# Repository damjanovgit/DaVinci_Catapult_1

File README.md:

# DaVinci_Catapult_1

This project is done as practical part of subjects Computer electronics and Microcontroller systems in academic 2022/23 year, winter semester. 
For realisation, we had to design PCB with all components that we need to control stepper motors, which are used to position the catapult, then limit switches and lasers, and the final result, our catapult, is shown on picture below.
<p align="center">

## Connection instructions

### PCB power supply

First, we need to connect 12V supply to PCB, and we use proto-board as voltage source to input pins of LM317. Black wire is connected to the ground, and red one to +12V. (Note: on this proto-board is written that it gives +15V but in reality it is +12V voltage source, so it is recommended to always check all sources with multimeter).
<p align="center">

 ### Connecting Picket3 programmer to PCB
 
 For programming microcontroller we use Picket3 programmer, and it has 5 wires that need to be connected in proper way. At the pictures bellow we have shown Picket3 pinout and its connection to PCB.
 <p align="center">

 ### Stepper motor and laser connection
 Six stepper motors were used to operate the catapult. Of that number, two stepper motors are used to move the lasers, the remaining four are on the catapult itself.
 Connectors for stepper motors are marked with numbers 1, 2, 3 and 4 and they need to be placed as it is shown on the picture.
 Two connectors that are next to these are used for lasers, and it is important that whichever laser we connect next to connector 4 is considered as upper laser(goes on the left side of catapult).
 <p align="center">

 Power supply for lasers is connected as it is shown on next picture, wires for every laser go in pairs (+ -, + -). Next to this we connect limit switches(next 4 pins).
 
  <p align="center">

 ### Connecting to a computer
 
 For this, we use USB to UART converter that allows us to connect a device with a UART interface to a computer via a USB port.
  <p align="center">

When everything is propperly connected, it is necessary to enable the programming of the microcontroller on the board, and after this has been successfully completed, we can control the catapult. Controlling the catapult and lasers is done by entering appropriate characters into the serial communication terminal. The table below represents the commands with the corresponding characters and description.

| Command | Functionality |
| :------: | :------: | 
| a | Laser 1 left rotation |
| d | Laser 1 right rotation |
| s | Stop laser 1 rotation |
| j | Laser 2 left rotation |
| l | Laser 2 right rotation |
| k | Stop laser 2 rotation |
| c | Calibration |
| f | Launch |
| p | Positioning of the catapult |
| b | Rotate catapult left |
| m | Rotate catapult right |
| n | Stop rotating |
| z | Tension management |
| u | Tension management |
| i | Firing |
| o | Firing |

Using the commands a, d, j and l we control the lasers by turning them left or right until we aim at the target. When the laser rays are intersected, it means that the target is aimed, and we stop their movement with the s and k commands. Once we have determined the position of the target, we use the p command to position the catapult so that it is ready for launch. Then, use command f to fire a cannonball. Using the b, m, n, z, u, i, o commands, manual control of all other motors is enabled for testing purposes.

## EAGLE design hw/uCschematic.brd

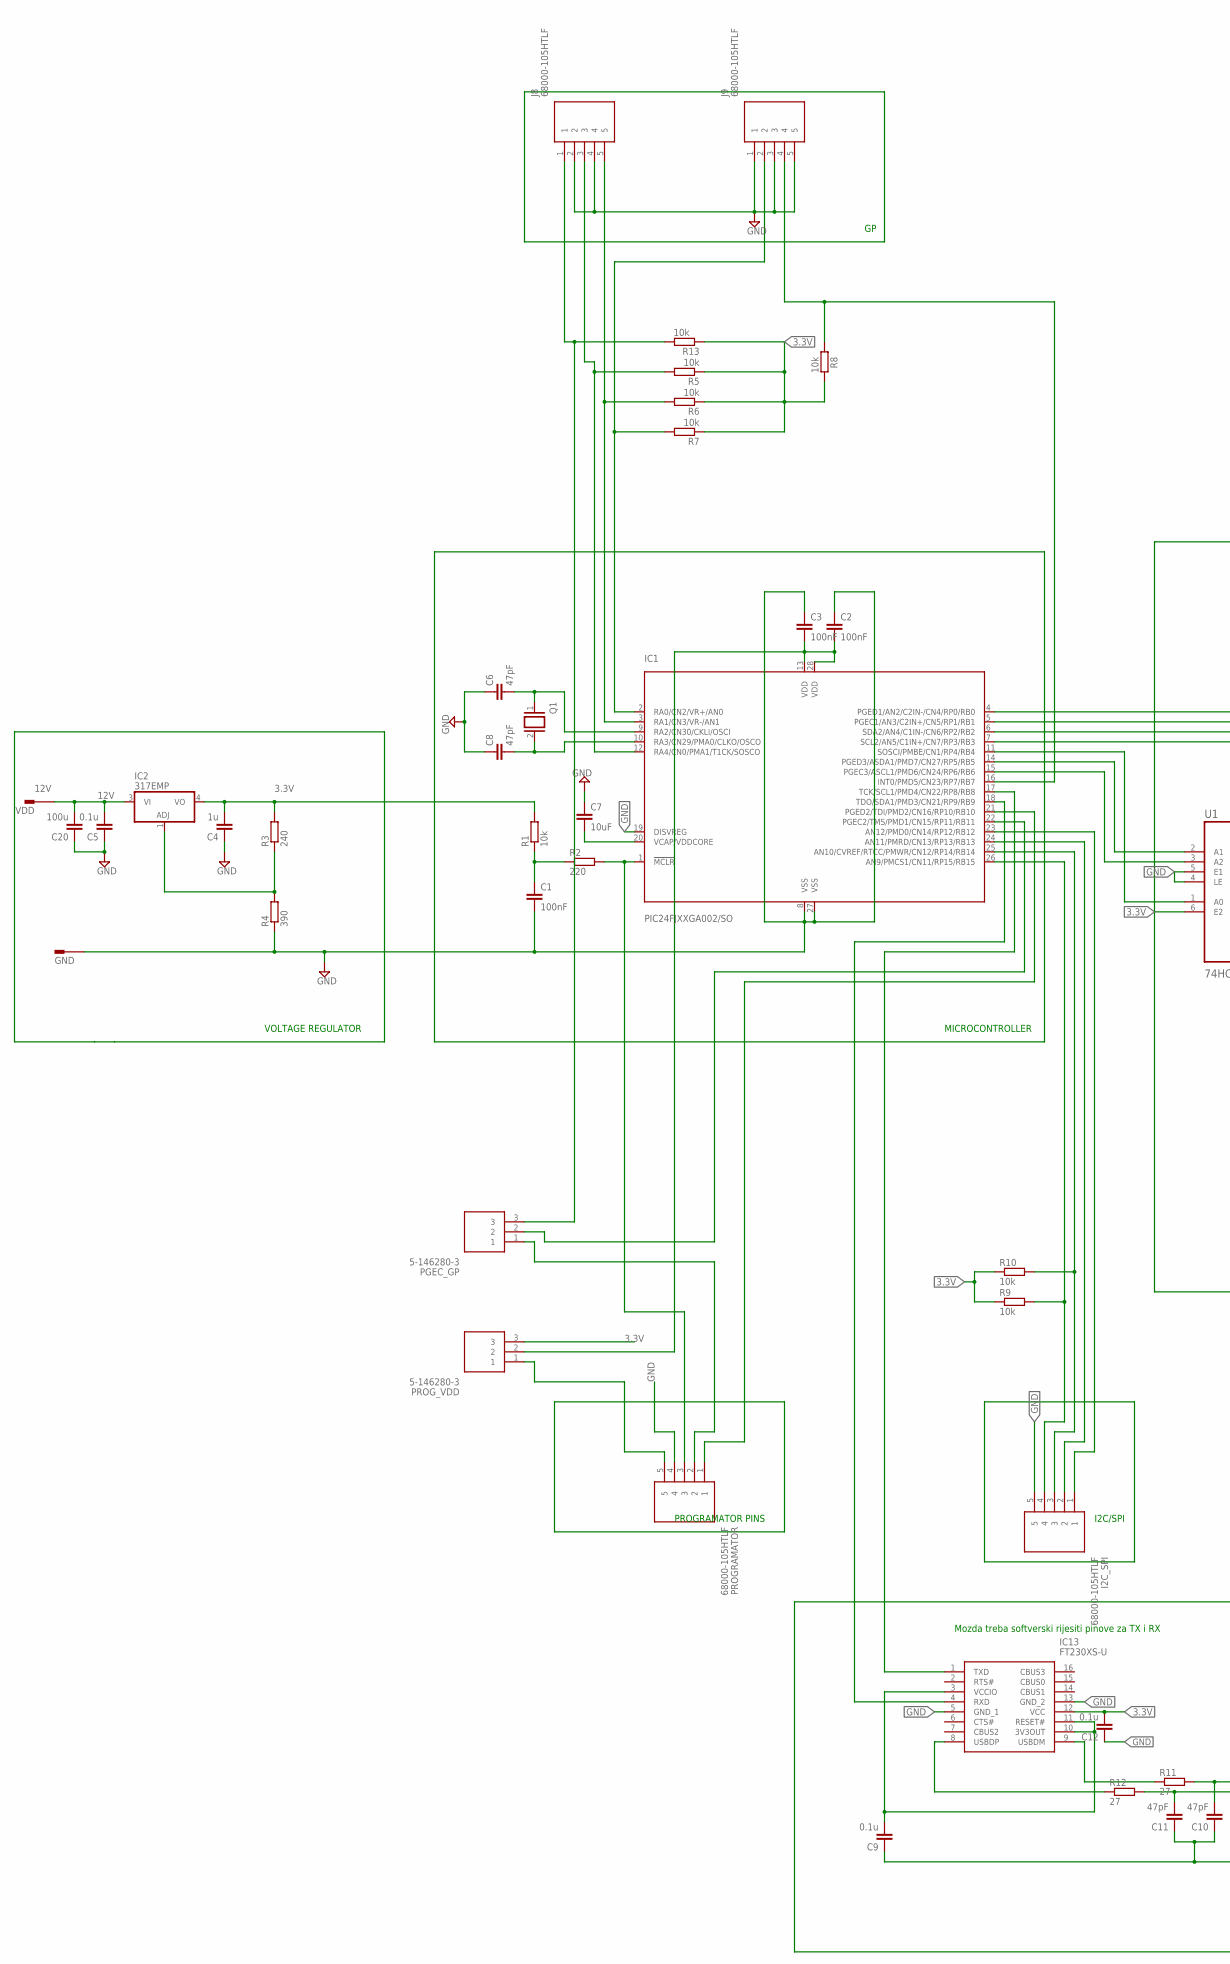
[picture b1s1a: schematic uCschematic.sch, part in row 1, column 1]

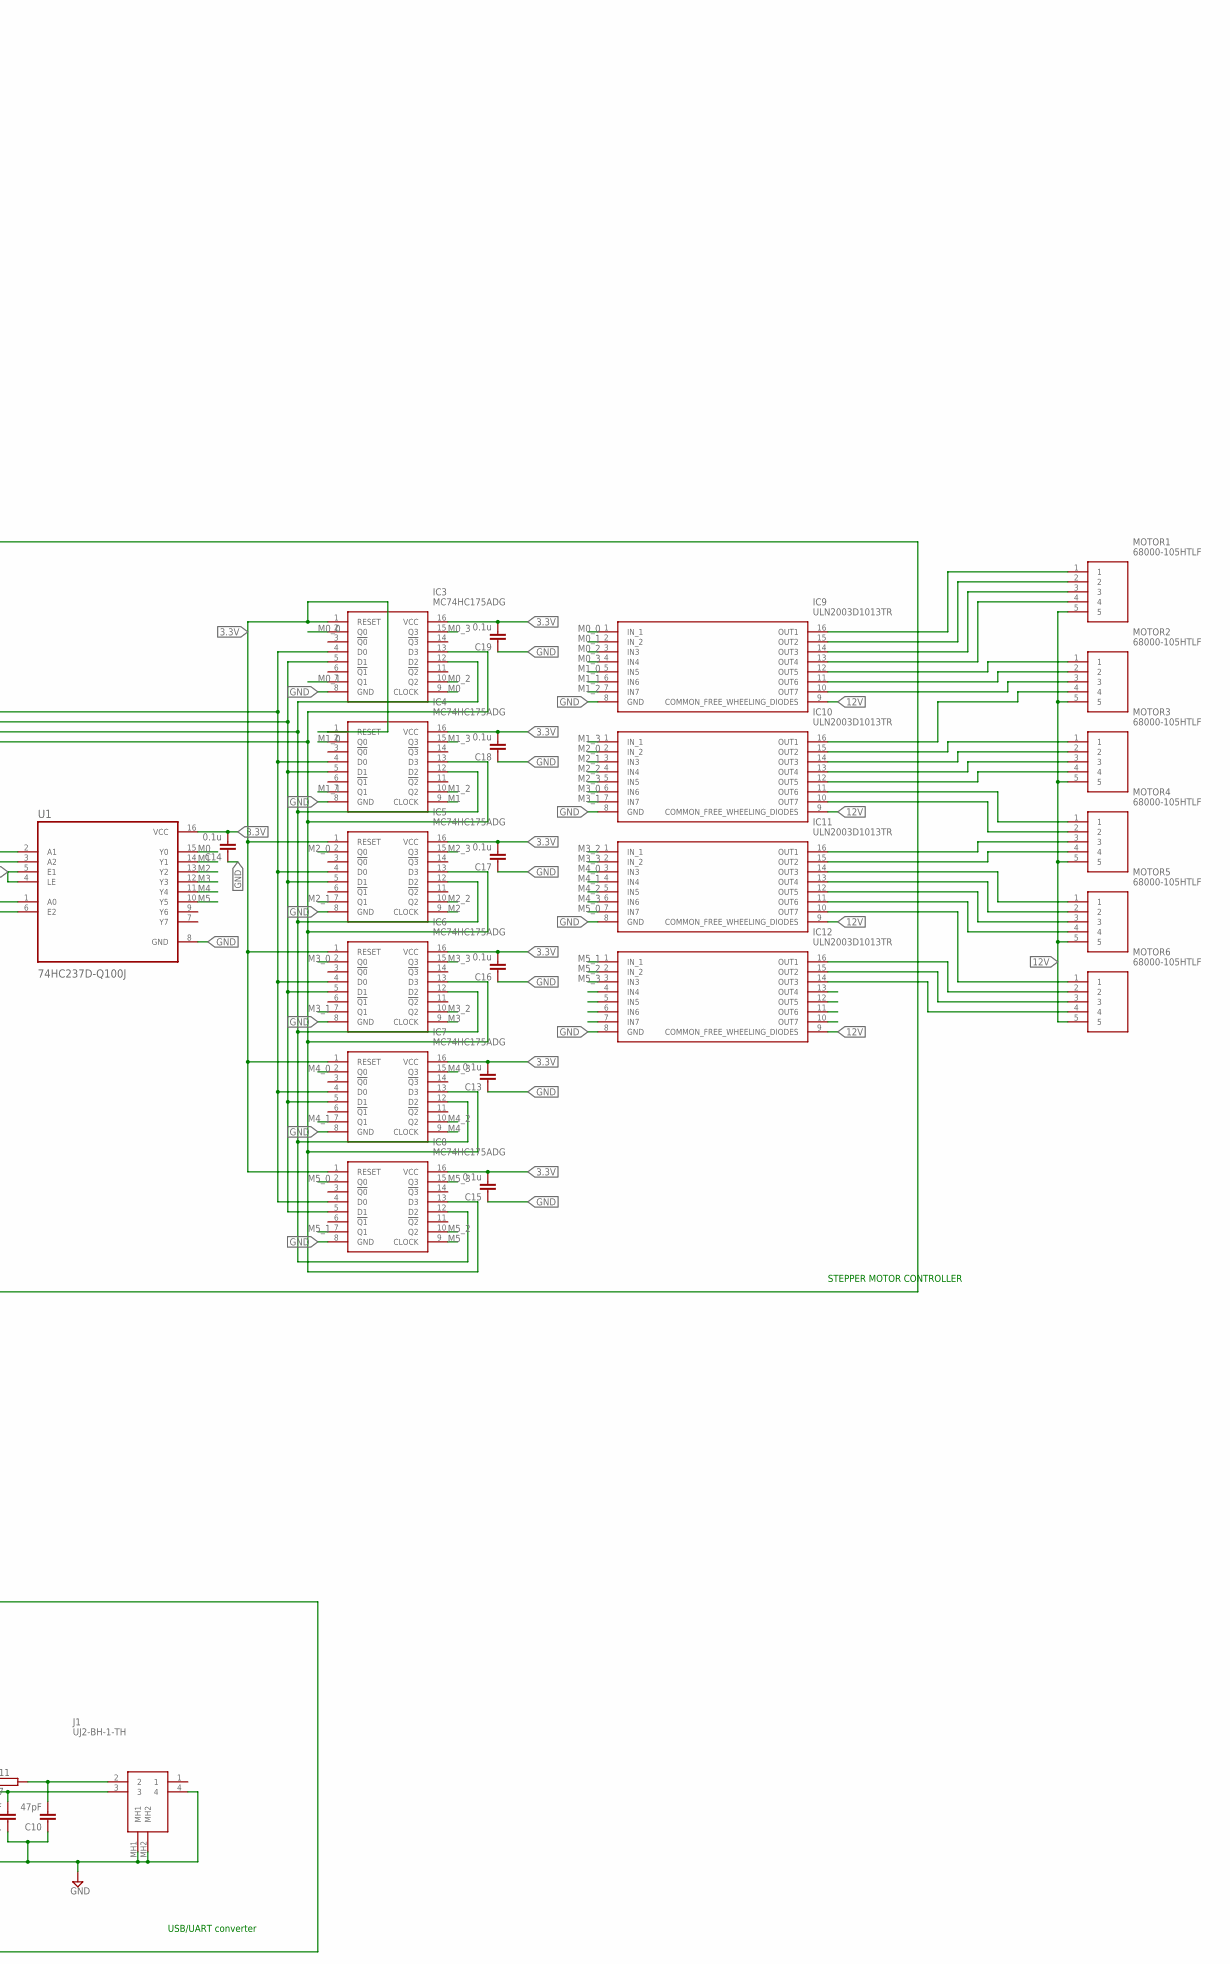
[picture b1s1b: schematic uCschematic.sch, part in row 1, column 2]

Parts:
C1, C2, C3: 100nF; C0805
C4: 1u; C0805
C5, C9, C12, C13, C14, C15, C16, C17, C18, C19: 0.1u; C0805
C6, C8, C10, C11: 47pF; C0805
C7: 10uF; C0805
C20: 100u; C0805
GND: PIN1-2; 62221
I2C_SPI: 68000-105HTLF; HDRV5W67P0X254_1X5_1270X241X85
IC1: PIC24FJXXGA002/SO; SO28W
IC2: 317EMP; SOT223
IC3, IC4, IC5, IC6, IC7, IC8: MC74HC175ADG; SOIC127P600X175-16N
IC9, IC10, IC11, IC12: ULN2003D1013TR; SOIC127P600X175-16N
IC13: FT230XS-U; SOP64P599X175-16N
J1: UJ2-BH-1-TH; UJ2BH1TH
J8, J9: 68000-105HTLF; HDRV5W67P0X254_1X5_1270X241X85
MOTOR1, MOTOR2, MOTOR3, MOTOR4, MOTOR5, MOTOR6: 68000-105HTLF; HDRV5W67P0X254_1X5_1270X241X85
PGEC_GP: 5-146280-3; HDRV3W97P0X254_1X3_721X234X821
PROGRAMATOR: 68000-105HTLF; HDRV5W67P0X254_1X5_1270X241X85
PROG_VDD: 5-146280-3; HDRV3W97P0X254_1X3_721X234X821
Q1: XTAL/S; QS
R1, R5, R6, R7, R8, R9, R10, R13: 10k; R0805
R2: 220; R0805
R3: 240; R0805
R4: 390; R0805
R11, R12: 27; R0805
U1: 74HC237D-Q100J; SOIC127P600X175-16N
VDD: 12V; 62221

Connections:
3.3V: C4.2, C12.2, C13.2, C14.2, C15.2, C16.2, C17.2, C18.2, C19.2, IC2.4 (VO), IC3.1 (RESET), IC3.16 (VCC), IC4.1 (RESET), IC4.16 (VCC), IC5.1 (RESET), IC5.16 (VCC), IC6.1 (RESET), IC6.16 (VCC), IC7.1 (RESET), IC7.16 (VCC), IC8.1 (RESET), IC8.16 (VCC), IC13.12 (VCC), PROG_VDD.3, R1.2, R3.2, R5.1, R6.1, R7.1, R8.2, R9.1, R10.1, R13.1, U1.6 (E2), U1.16 (VCC)
12V: C5.2, C20.2, IC2.3 (VI), IC9.9 (COMMON_FREE_WHEELING_DIODES), IC10.9 (COMMON_FREE_WHEELING_DIODES), IC11.9 (COMMON_FREE_WHEELING_DIODES), IC12.9 (COMMON_FREE_WHEELING_DIODES), MOTOR1.5, MOTOR2.5, MOTOR3.5, MOTOR4.5, MOTOR5.5, MOTOR6.5, VDD.1
GND: C1.2, C2.1, C3.1, C4.1, C5.1, C6.1, C7.1, C8.1, C9.1, C10.1, C11.1, C12.1, C14.1, C20.1, GND.1, I2C_SPI.5, IC1.8 (VSS), IC1.19 (DISVREG), IC1.27 (VSS), IC3.8 (GND), IC4.8 (GND), IC5.8 (GND), IC6.8 (GND), IC7.8 (GND), IC8.8 (GND), IC9.8 (GND), IC10.8 (GND), IC11.8 (GND), IC12.8 (GND), IC13.5 (GND_1), IC13.13 (GND_2), J1.4, J1.MH1, J1.MH2, J8.2, J8.4, J9.1, J9.3, J9.5, PROGRAMATOR.4, R4.1, U1.4 (LE), U1.5 (E1), U1.8 (GND)
GP_OKIDAC: J8.1, PGEC_GP.3, R13.2
M0: IC3.9 (CLOCK), U1.15 (Y0)
M0_0: IC3.2 (Q0), IC9.1 (IN_1)
M0_1: IC3.7 (Q1), IC9.2 (IN_2)
M0_2: IC3.10 (Q2), IC9.3 (IN3)
M0_3: IC3.15 (Q3), IC9.4 (IN4)
M1: IC4.9 (CLOCK), U1.14 (Y1)
M1_0: IC4.2 (Q0), IC9.5 (IN5)
M1_1: IC4.7 (Q1), IC9.6 (IN6)
M1_2: IC4.10 (Q2), IC9.7 (IN7)
M1_3: IC4.15 (Q3), IC10.1 (IN_1)
M2: IC5.9 (CLOCK), U1.13 (Y2)
M2_0: IC5.2 (Q0), IC10.2 (IN_2)
M2_1: IC5.7 (Q1), IC10.3 (IN3)
M2_2: IC5.10 (Q2), IC10.4 (IN4)
M2_3: IC5.15 (Q3), IC10.5 (IN5)
M3: IC6.9 (CLOCK), U1.12 (Y3)
M3_0: IC6.2 (Q0), IC10.6 (IN6)
M3_1: IC6.7 (Q1), IC10.7 (IN7)
M3_2: IC6.10 (Q2), IC11.1 (IN_1)
M3_3: IC6.15 (Q3), IC11.2 (IN_2)
M4: IC7.9 (CLOCK), U1.11 (Y4)
M4_0: IC7.2 (Q0), IC11.3 (IN3)
M4_1: IC7.7 (Q1), IC11.4 (IN4)
M4_2: IC7.10 (Q2), IC11.5 (IN5)
M4_3: IC7.15 (Q3), IC11.6 (IN6)
M5: IC8.9 (CLOCK), U1.10 (Y5)
M5_0: IC8.2 (Q0), IC11.7 (IN7)
M5_1: IC8.7 (Q1), IC12.1 (IN_1)
M5_2: IC8.10 (Q2), IC12.2 (IN_2)
M5_3: IC8.15 (Q3), IC12.3 (IN3)
unnamed: C1.1, R1.1, R2.1
unnamed: IC1.1 (!MCLR), PROGRAMATOR.3, R2.2
unnamed: C7.2, IC1.20 (VCAP/VDDCORE)
unnamed: C2.2, C3.2, IC1.13 (VDD), IC1.28 (VDD), PROG_VDD.2
unnamed: C6.2, IC1.9 (RA2/CN30/CKLI/OSCI), Q1.1
unnamed: IC1.21 (PGED2/TDI/PMD2/CN16/RP10/RB10), PROGRAMATOR.1
unnamed: C8.2, IC1.10 (RA3/CN29/PMA0/CLKO/OSCO), Q1.2
unnamed: IC2.1 (ADJ), R3.1, R4.2
unnamed: IC1.7 (SCL2/AN5/C1IN+/CN7/RP3/RB3), IC3.13 (D3), IC4.13 (D3), IC5.13 (D3), IC6.13 (D3), IC7.13 (D3), IC8.13 (D3)
unnamed: IC1.6 (SDA2/AN4/C1IN-/CN6/RP2/RB2), IC3.12 (D2), IC4.12 (D2), IC5.12 (D2), IC6.12 (D2), IC7.12 (D2), IC8.12 (D2)
unnamed: IC1.11 (SOSCI/PMBE/CN1/RP4/RB4), U1.1 (A0)
unnamed: IC1.14 (PGED3/ASDA1/PMD7/CN27/RP5/RB5), U1.2 (A1)
unnamed: IC1.15 (PGEC3/ASCL1/PMD6/CN24/RP6/RB6), U1.3 (A2)
unnamed: IC1.12 (RA4/CN0/PMA1/T1CK/SOSCO), J8.3, R5.2
unnamed: IC1.5 (PGEC1/AN3/C2IN+/CN5/RP1/RB1), IC3.5 (D1), IC4.5 (D1), IC5.5 (D1), IC6.5 (D1), IC7.5 (D1), IC8.5 (D1)
unnamed: IC1.4 (PGED1/AN2/C2IN-/CN4/RP0/RB0), IC3.4 (D0), IC4.4 (D0), IC5.4 (D0), IC6.4 (D0), IC7.4 (D0), IC8.4 (D0)
unnamed: IC1.22 (PGEC2/TMS/PMD1/CN15/RP11/RB11), PGEC_GP.2
unnamed: IC1.18 (TDO/SDA1/PMD3/CN21/RP9/RB9), IC13.4 (RXD)
unnamed: IC1.17 (TCK/SCL1/PMD4/CN22/RP8/RB8), IC13.1 (TXD)
unnamed: PROGRAMATOR.5, PROG_VDD.1
unnamed: PGEC_GP.1, PROGRAMATOR.2
unnamed: IC1.3 (RA1/CN3/VR-/AN1), J8.5, R6.2
unnamed: IC9.16 (OUT1), MOTOR1.1
unnamed: IC9.15 (OUT2), MOTOR1.2
unnamed: IC9.14 (OUT3), MOTOR1.3
unnamed: IC9.13 (OUT4), MOTOR1.4
unnamed: IC9.12 (OUT5), MOTOR2.1
unnamed: IC9.11 (OUT6), MOTOR2.2
unnamed: IC9.10 (OUT7), MOTOR2.3
unnamed: IC1.2 (RA0/CN2/VR+/AN0), J9.2, R7.2
unnamed: IC1.16 (INT0/PMD5/CN23/RP7/RB7), J9.4, R8.1
unnamed: I2C_SPI.1, IC1.23 (AN12/PMD0/CN14/RP12/RB12)
unnamed: I2C_SPI.2, IC1.24 (AN11/PMRD/CN13/RP13/RB13)
unnamed: I2C_SPI.3, IC1.25 (AN10/CVREF/RTCC/PMWR/CN12/RP14/RB14), R10.2
unnamed: I2C_SPI.4, IC1.26 (AN9/PMCS1/CN11/RP15/RB15), R9.2
unnamed: C10.2, J1.2, R11.2
unnamed: IC10.16 (OUT1), MOTOR2.4
unnamed: IC10.15 (OUT2), MOTOR3.1
unnamed: IC10.14 (OUT3), MOTOR3.2
unnamed: IC10.13 (OUT4), MOTOR3.3
unnamed: IC10.12 (OUT5), MOTOR3.4
unnamed: IC10.11 (OUT6), MOTOR4.1
unnamed: IC10.10 (OUT7), MOTOR4.2
unnamed: C9.2, IC13.3 (VCCIO), IC13.10 (3V3OUT), IC13.11 (RESET#)
unnamed: C11.2, J1.3, R12.2
unnamed: IC13.9 (USBDM), R11.1
unnamed: IC13.8 (USBDP), R12.1
unnamed: IC12.15 (OUT2), MOTOR6.3
unnamed: IC11.16 (OUT1), MOTOR4.3
unnamed: IC11.15 (OUT2), MOTOR4.4
unnamed: IC11.14 (OUT3), MOTOR5.1
unnamed: IC11.13 (OUT4), MOTOR5.2
unnamed: IC11.12 (OUT5), MOTOR5.3
unnamed: IC11.11 (OUT6), MOTOR5.4
unnamed: IC11.10 (OUT7), MOTOR6.1
unnamed: IC12.16 (OUT1), MOTOR6.2
unnamed: IC12.14 (OUT3), MOTOR6.4

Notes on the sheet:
VOLTAGE REGULATOR
MICROCONTROLLER
STEPPER MOTOR CONTROLLER
PROGRAMATOR PINS
I2C/SPI
Mozda treba softverski rijesiti pinove za TX i RX
USB/UART converter

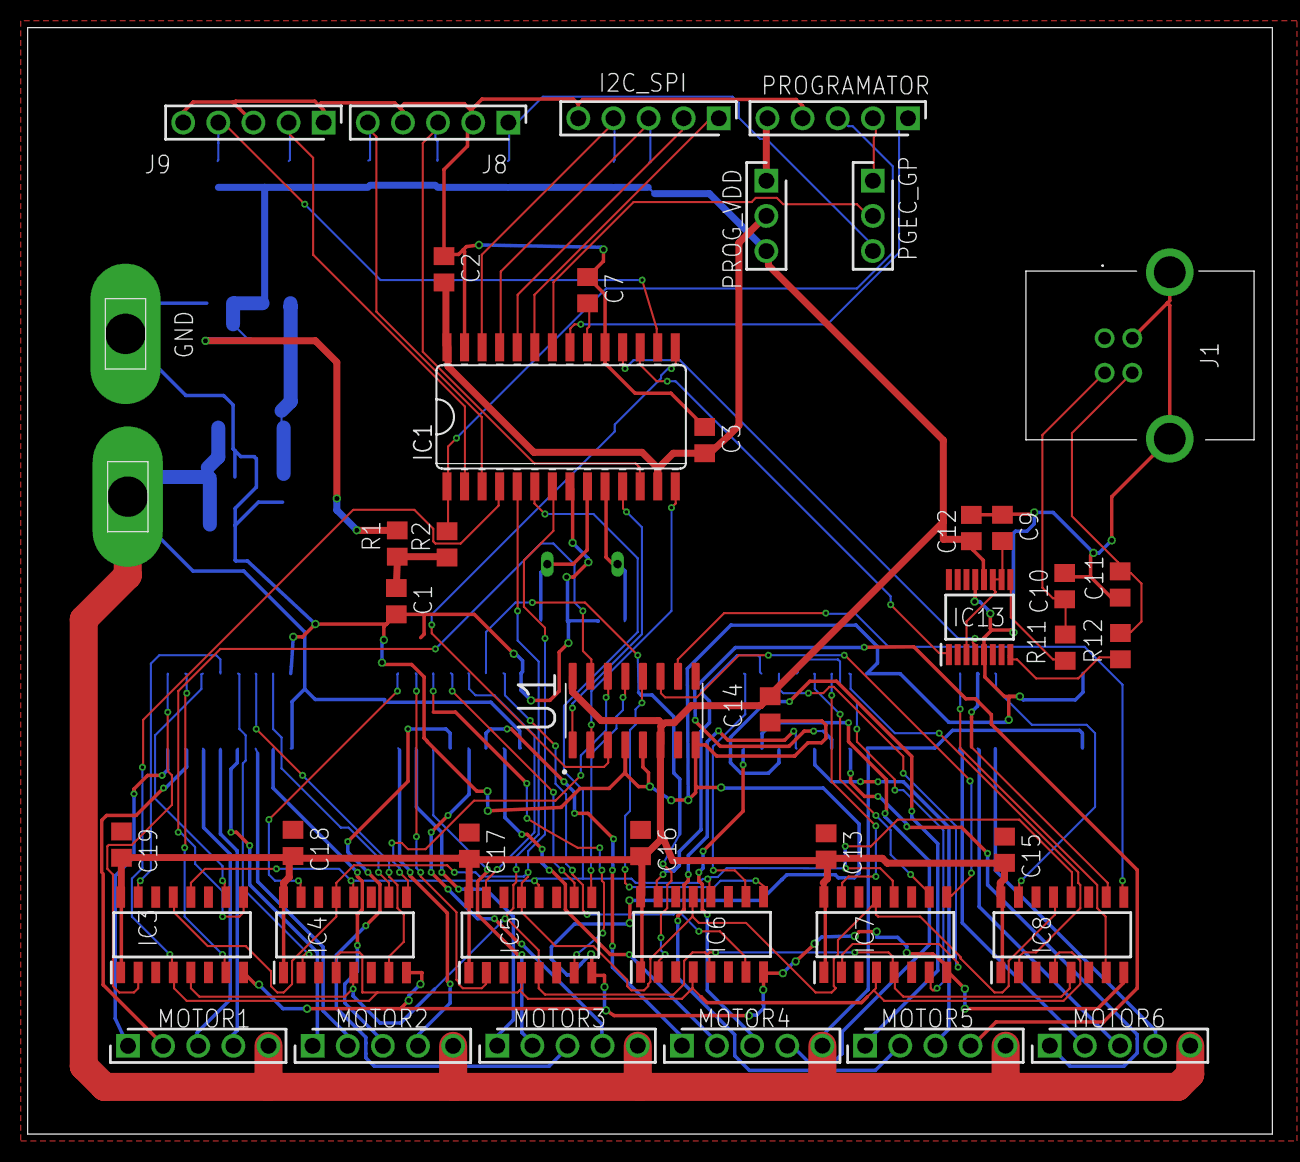
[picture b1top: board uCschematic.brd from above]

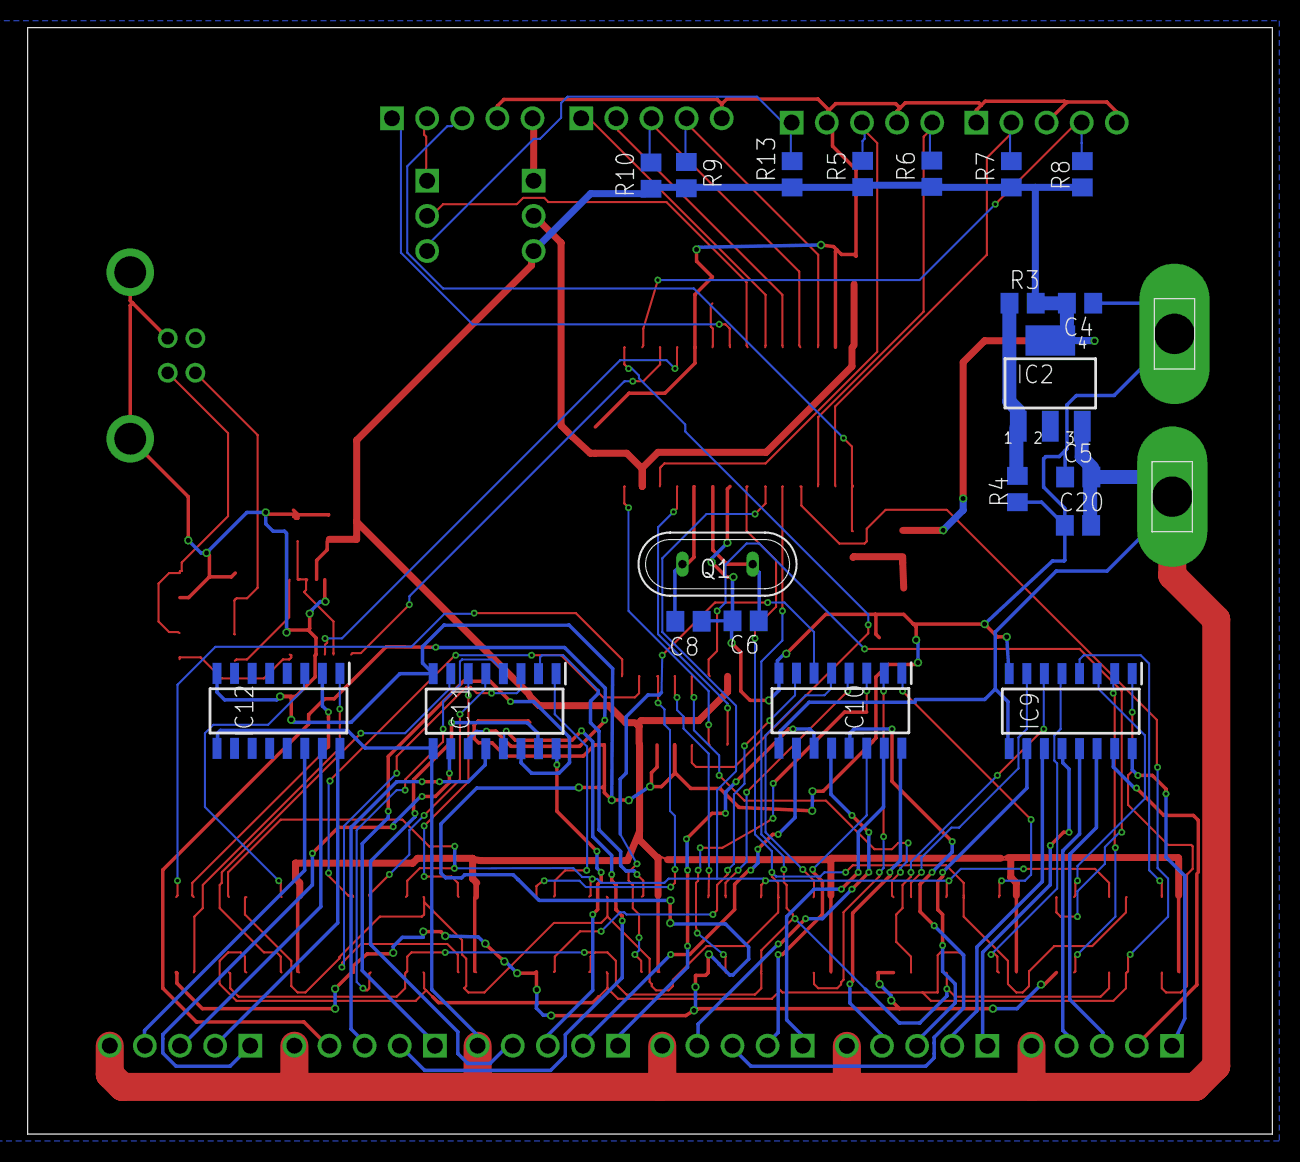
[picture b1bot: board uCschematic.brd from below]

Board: 2 copper layers, 90.0 x 80.0 mm, 63 parts (20 on the bottom side), 91 nets.

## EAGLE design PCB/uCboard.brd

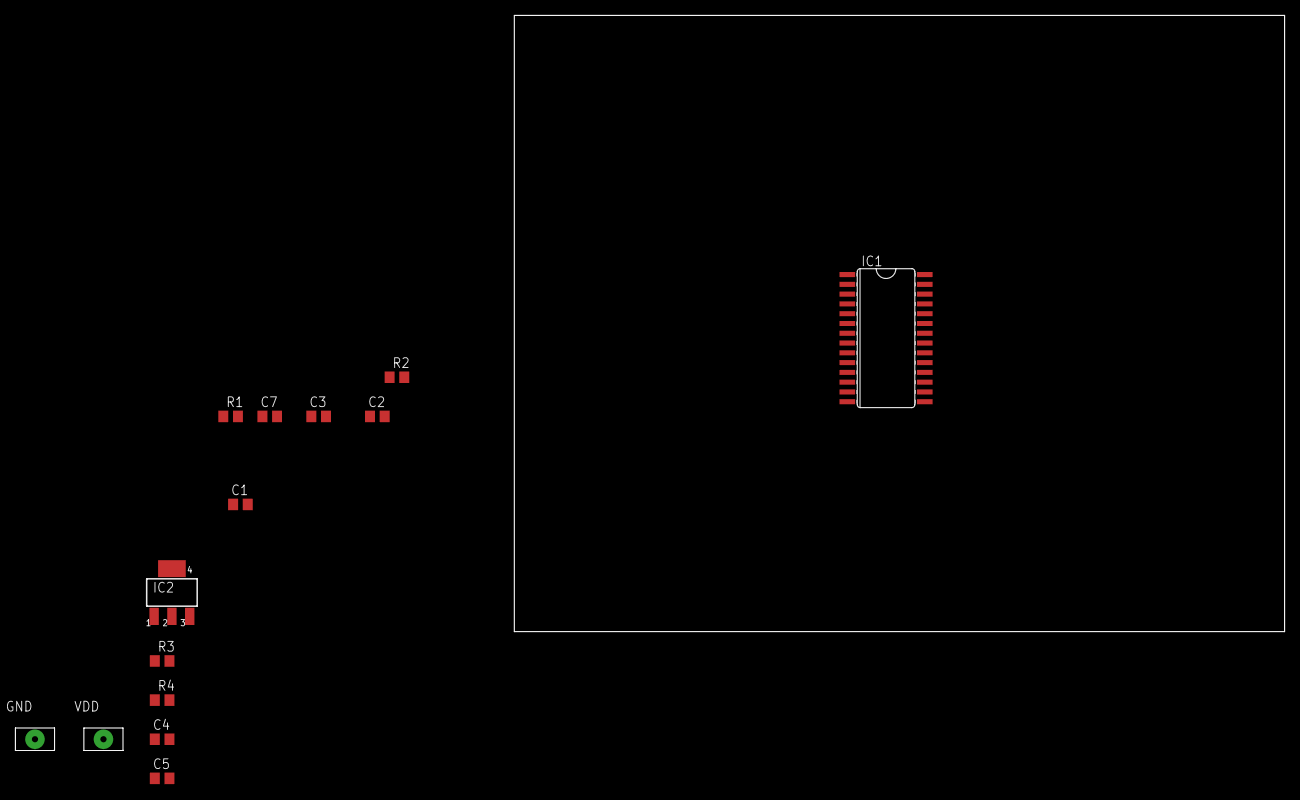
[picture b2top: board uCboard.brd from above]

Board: 2 copper layers, 164.8 x 95.4 mm, 14 parts (0 on the bottom side), 11 nets, no tracks yet.

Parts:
C1, C2, C3: 100nF; C0805
C4, C5: C0805
C7: 10uF; C0805
GND: PIN1-2; 62221
IC1: PIC24FJXXGA002/SO; SO28W
IC2: 317EMP; SOT223
R1: 10k; R0805
R2: 220; R0805
R3: 470; R0805
R4: 770,8; R0805
VDD: 12V; 62221

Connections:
3.3V: C4.2, IC2.4, R1.2, R3.2
GND: C1.2, C4.1, C5.1, C7.1, GND.1, R4.1
unnamed: C1.1, R1.1, R2.1
unnamed: IC1.1, R2.2
unnamed: C7.2, IC1.20
unnamed: C3.2, IC1.13
unnamed: C2.2, IC1.28
unnamed: C3.1, IC1.8
unnamed: C2.1, IC1.27
unnamed: C5.2, IC2.3, VDD.1
unnamed: IC2.1, R3.1, R4.2

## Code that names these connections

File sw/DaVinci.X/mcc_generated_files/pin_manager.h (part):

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*/
/**
  @Summary
    Sets the GPIO pin, RA0, high using LATA0.

  @Description
    Sets the GPIO pin, RA0, high using LATA0.

  @Preconditions
    The RA0 must be set to an output.
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#define GP4_SetHigh()          (_LATA0 = 1)
/**
  @Summary
    Sets the GPIO pin, RA0, low using LATA0.

  @Description
    Sets the GPIO pin, RA0, low using LATA0.

  @Preconditions
    The RA0 must be set to an output.
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#define GP4_SetLow()           (_LATA0 = 0)
/**
  @Summary
    Toggles the GPIO pin, RA0, using LATA0.

  @Description
    Toggles the GPIO pin, RA0, using LATA0.

  @Preconditions
    The RA0 must be set to an output.
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#define GP4_Toggle()           (_LATA0 ^= 1)
/**
  @Summary
    Reads the value of the GPIO pin, RA0.

  @Description
    Reads the value of the GPIO pin, RA0.

  @Preconditions
    None.
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    </code>

*/
#define GP4_GetValue()         _RA0
/**
  @Summary
    Configures the GPIO pin, RA0, as an input.

  @Description
    Configures the GPIO pin, RA0, as an input.

  @Preconditions
    None.
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#define GP4_SetDigitalInput()  (_TRISA0 = 1)
/**
  @Summary
    Configures the GPIO pin, RA0, as an output.

  @Description
    Configures the GPIO pin, RA0, as an output.

  @Preconditions
    None.
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#define GP4_SetDigitalOutput() (_TRISA0 = 0)
/**
  @Summary
    Sets the GPIO pin, RA1, high using LATA1.

  @Description
    Sets the GPIO pin, RA1, high using LATA1.

  @Preconditions
    The RA1 must be set to an output.
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#define GP3_SetHigh()          (_LATA1 = 1)
/**
  @Summary
    Sets the GPIO pin, RA1, low using LATA1.

  @Description
    Sets the GPIO pin, RA1, low using LATA1.

  @Preconditions
    The RA1 must be set to an output.
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#define GP3_SetLow()           (_LATA1 = 0)
/**
  @Summary
    Toggles the GPIO pin, RA1, using LATA1.

  @Description
    Toggles the GPIO pin, RA1, using LATA1.

  @Preconditions
    The RA1 must be set to an output.
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#define GP3_Toggle()           (_LATA1 ^= 1)
/**
  @Summary
    Reads the value of the GPIO pin, RA1.

  @Description
    Reads the value of the GPIO pin, RA1.

  @Preconditions
    None.
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    </code>

*/
#define GP3_GetValue()         _RA1
/**
  @Summary
    Configures the GPIO pin, RA1, as an input.

  @Description
    Configures the GPIO pin, RA1, as an input.

  @Preconditions
    None.
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#define GP3_SetDigitalInput()  (_TRISA1 = 1)
/**
  @Summary
    Configures the GPIO pin, RA1, as an output.

  @Description
    Configures the GPIO pin, RA1, as an output.

  @Preconditions
    None.
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#define GP3_SetDigitalOutput() (_TRISA1 = 0)
/**
  @Summary
    Sets the GPIO pin, RA4, high using LATA4.

  @Description
    Sets the GPIO pin, RA4, high using LATA4.

  @Preconditions
    The RA4 must be set to an output.
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#define GP2_SetHigh()          (_LATA4 = 1)
/**
  @Summary
    Sets the GPIO pin, RA4, low using LATA4.

  @Description
    Sets the GPIO pin, RA4, low using LATA4.

  @Preconditions
    The RA4 must be set to an output.
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#define GP2_SetLow()           (_LATA4 = 0)
/**
  @Summary
    Toggles the GPIO pin, RA4, using LATA4.

  @Description
    Toggles the GPIO pin, RA4, using LATA4.

  @Preconditions
    The RA4 must be set to an output.
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#define GP2_Toggle()           (_LATA4 ^= 1)
/**
  @Summary
    Reads the value of the GPIO pin, RA4.

  @Description
    Reads the value of the GPIO pin, RA4.

  @Preconditions
    None.
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    </code>

*/
#define GP2_GetValue()         _RA4
/**
  @Summary
    Configures the GPIO pin, RA4, as an input.

  @Description
    Configures the GPIO pin, RA4, as an input.

  @Preconditions
    None.
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#define GP2_SetDigitalInput()  (_TRISA4 = 1)
/**
  @Summary
    Configures the GPIO pin, RA4, as an output.

  @Description
    Configures the GPIO pin, RA4, as an output.

  @Preconditions
    None.
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#define GP2_SetDigitalOutput() (_TRISA4 = 0)
/**
  @Summary
    Sets the GPIO pin, RB0, high using LATB0.

  @Description
    Sets the GPIO pin, RB0, high using LATB0.

  @Preconditions
    The RB0 must be set to an output.
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#define BUS0_SetHigh()          (_LATB0 = 1)
/**
  @Summary
    Sets the GPIO pin, RB0, low using LATB0.

  @Description
    Sets the GPIO pin, RB0, low using LATB0.

  @Preconditions
    The RB0 must be set to an output.
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#define BUS0_SetLow()           (_LATB0 = 0)
/**
  @Summary
    Toggles the GPIO pin, RB0, using LATB0.

  @Description
    Toggles the GPIO pin, RB0, using LATB0.

  @Preconditions
    The RB0 must be set to an output.
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#define BUS0_Toggle()           (_LATB0 ^= 1)
/**
  @Summary
    Reads the value of the GPIO pin, RB0.

  @Description
    Reads the value of the GPIO pin, RB0.

  @Preconditions
    None.
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    </code>

*/
#define BUS0_GetValue()         _RB0
/**
  @Summary
    Configures the GPIO pin, RB0, as an input.

  @Description
    Configures the GPIO pin, RB0, as an input.

  @Preconditions
    None.
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#define BUS0_SetDigitalInput()  (_TRISB0 = 1)
/**
  @Summary
    Configures the GPIO pin, RB0, as an output.

  @Description
    Configures the GPIO pin, RB0, as an output.

  @Preconditions
    None.
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#define BUS0_SetDigitalOutput() (_TRISB0 = 0)
/**
  @Summary
    Sets the GPIO pin, RB1, high using LATB1.

  @Description
    Sets the GPIO pin, RB1, high using LATB1.

  @Preconditions
    The RB1 must be set to an output.
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#define BUS1_SetHigh()          (_LATB1 = 1)
/**
  @Summary
    Sets the GPIO pin, RB1, low using LATB1.

  @Description
    Sets the GPIO pin, RB1, low using LATB1.

  @Preconditions
    The RB1 must be set to an output.
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#define BUS1_SetLow()           (_LATB1 = 0)
/**
  @Summary
    Toggles the GPIO pin, RB1, using LATB1.

  @Description
    Toggles the GPIO pin, RB1, using LATB1.

  @Preconditions
    The RB1 must be set to an output.
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#define BUS1_Toggle()           (_LATB1 ^= 1)
/**
  @Summary
    Reads the value of the GPIO pin, RB1.

  @Description
    Reads the value of the GPIO pin, RB1.

  @Preconditions
    None.
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    </code>

*/
#define BUS1_GetValue()         _RB1
/**
  @Summary
    Configures the GPIO pin, RB1, as an input.

  @Description
    Configures the GPIO pin, RB1, as an input.

  @Preconditions
    None.
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#define BUS1_SetDigitalInput()  (_TRISB1 = 1)
/**
  @Summary
    Configures the GPIO pin, RB1, as an output.

  @Description
    Configures the GPIO pin, RB1, as an output.

  @Preconditions
    None.
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#define BUS1_SetDigitalOutput() (_TRISB1 = 0)
/**
  @Summary
    Sets the GPIO pin, RB10, high using LATB10.

  @Description
    Sets the GPIO pin, RB10, high using LATB10.

  @Preconditions
    The RB10 must be set to an output.
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#define PGDED2_SetHigh()          (_LATB10 = 1)
/**
  @Summary
    Sets the GPIO pin, RB10, low using LATB10.

  @Description
    Sets the GPIO pin, RB10, low using LATB10.

  @Preconditions
    The RB10 must be set to an output.
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#define PGDED2_SetLow()           (_LATB10 = 0)
/**
  @Summary
    Toggles the GPIO pin, RB10, using LATB10.

  @Description
    Toggles the GPIO pin, RB10, using LATB10.

  @Preconditions
    The RB10 must be set to an output.
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#define PGDED2_Toggle()           (_LATB10 ^= 1)
/**
  @Summary
    Reads the value of the GPIO pin, RB10.

  @Description
    Reads the value of the GPIO pin, RB10.

  @Preconditions
    None.
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    </code>

*/
#define PGDED2_GetValue()         _RB10
/**
  @Summary
    Configures the GPIO pin, RB10, as an input.

  @Description
    Configures the GPIO pin, RB10, as an input.

  @Preconditions
    None.
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#define PGDED2_SetDigitalInput()  (_TRISB10 = 1)
/**
  @Summary
    Configures the GPIO pin, RB10, as an output.

  @Description
    Configures the GPIO pin, RB10, as an output.

  @Preconditions
    None.
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#define PGDED2_SetDigitalOutput() (_TRISB10 = 0)
/**
  @Summary
    Sets the GPIO pin, RB11, high using LATB11.

  @Description
    Sets the GPIO pin, RB11, high using LATB11.

  @Preconditions
    The RB11 must be set to an output.
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#define GP1_PGEC2_SetHigh()          (_LATB11 = 1)
/**
  @Summary
    Sets the GPIO pin, RB11, low using LATB11.

  @Description
    Sets the GPIO pin, RB11, low using LATB11.

  @Preconditions
    The RB11 must be set to an output.
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#define GP1_PGEC2_SetLow()           (_LATB11 = 0)
/**
  @Summary
    Toggles the GPIO pin, RB11, using LATB11.

  @Description
    Toggles the GPIO pin, RB11, using LATB11.

  @Preconditions
    The RB11 must be set to an output.
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#define GP1_PGEC2_Toggle()           (_LATB11 ^= 1)
/**
  @Summary
    Reads the value of the GPIO pin, RB11.

  @Description
    Reads the value of the GPIO pin, RB11.

  @Preconditions
    None.
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    </code>

*/
#define GP1_PGEC2_GetValue()         _RB11
/**
  @Summary
    Configures the GPIO pin, RB11, as an input.

  @Description
    Configures the GPIO pin, RB11, as an input.

  @Preconditions
    None.
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#define GP1_PGEC2_SetDigitalInput()  (_TRISB11 = 1)
/**
  @Summary
    Configures the GPIO pin, RB11, as an output.

  @Description
    Configures the GPIO pin, RB11, as an output.

  @Preconditions
    None.
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#define GP1_PGEC2_SetDigitalOutput() (_TRISB11 = 0)
/**
  @Summary
    Sets the GPIO pin, RB12, high using LATB12.

  @Description
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
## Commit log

2022-12-25 Added component documentation
2022-12-25 Inital schema
2022-12-25 Made block for each component
2022-12-25 Created lib folder
2022-12-27 Sredjena sema
2022-12-30 SPI, I2C, 4 granicna prekidaca, DONE
2023-01-05 Uradjene izmjene PIN19 spojen na GND Kapacitivnost kondenzatora kod kristala kvarca je sada 47pF Dodana je masa za svaki od GP Dodana je masa za SPI i I2C Dodane su mase za koracne motore LATCH i ENA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
2023-01-05 Dodana biblioteka za FT230XS-U UART/USB
2023-01-06 Uradjena sema za USB/UART converter
2023-01-06 -Dodani bajpas kondenzatori.
2023-01-06 -Unesene potrebne izmjene
2023-01-06 Osiguravanje dodatnog GP u slucaju da bude potreban.
2023-01-10 Šema u Proteusu za simulaciju rada step motora.
2023-01-10 Dodan csv file sa spiskom komponenata generisan pomoću Eagle-a
2023-01-11 Uradjena simulacija u proteusu USB micro AB -> USB type A Izvrsena simulacija u proteusu. Sve radi kako treba Izvrsene sitne izmjene na semi
2023-01-18 USB type A -> type B
2023-01-22 Postavljene komponente na PCB, potrebno rutirati
2023-01-22 Postavljene komponente na PCB
2023-01-23 Dodan kondenzator većeg kapaciteta na ulazu za napajanje
2023-01-24 - Rutiranje kontrolera za upravljanje stepper motorima - Dodavanje DRC fajla za dvoslojni PCB
2023-01-25 Rutiranje USB -a, graničnih prekidača i regulatora napona.
2023-01-25 Valjda gotovo
2023-02-01 Deleted unnecessarily vias
2023-02-01 PCB done
2023-02-01 Ispravke u rutiranju
2023-02-01 Addede drill and gerber files - check!
2023-02-02 Kreirani gerber, drill i BOM fajlovi
2023-02-07 BOM file changed
2023-03-25 Renamed folder PCB to hw
2023-03-25 Created initial software project
2023-03-26 Written initial version of main function Needs to update on every feature added
2023-03-26 Removed microsteps
2023-03-26 Some changes
2023-03-26 Written function for positioning catapult left/right
2023-03-26 Written main function for positioning catapult
2023-03-26 Small changes
2023-03-27 Updated functions for positioning and calculating angle
2023-03-29 Written function for calibration of pitch
2023-03-29 Main changed a bit
2023-03-30 Mostly done
2023-04-27 Impelented tightening function
2023-04-27 Update README.md
    Neke izmjene README fajla. Nije završeno.

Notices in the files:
sw/DaVinci.X/mcc_generated_files/pin_manager.h:
(c) 2020 Microchip Technology Inc. and its subsidiaries. You may use this
